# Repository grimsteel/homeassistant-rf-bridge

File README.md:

# Home Assistant RF + IR Bridge

A wireless module for adding RF and IR capabilities to Home Assistant. Built on an ESP32-S2. Uses the MQTT protocol.

## Firmware

A template ESPHome firmware is included in the `esphome` dir.

## Case

Case coming soon!

## PCB

* Front: includes pin sockets for two CC1101 modules. (allows for RX/TX on multiple freqs if needed)
* Back: space for two 6mm buttons, two IR leds, and one IR receiver.

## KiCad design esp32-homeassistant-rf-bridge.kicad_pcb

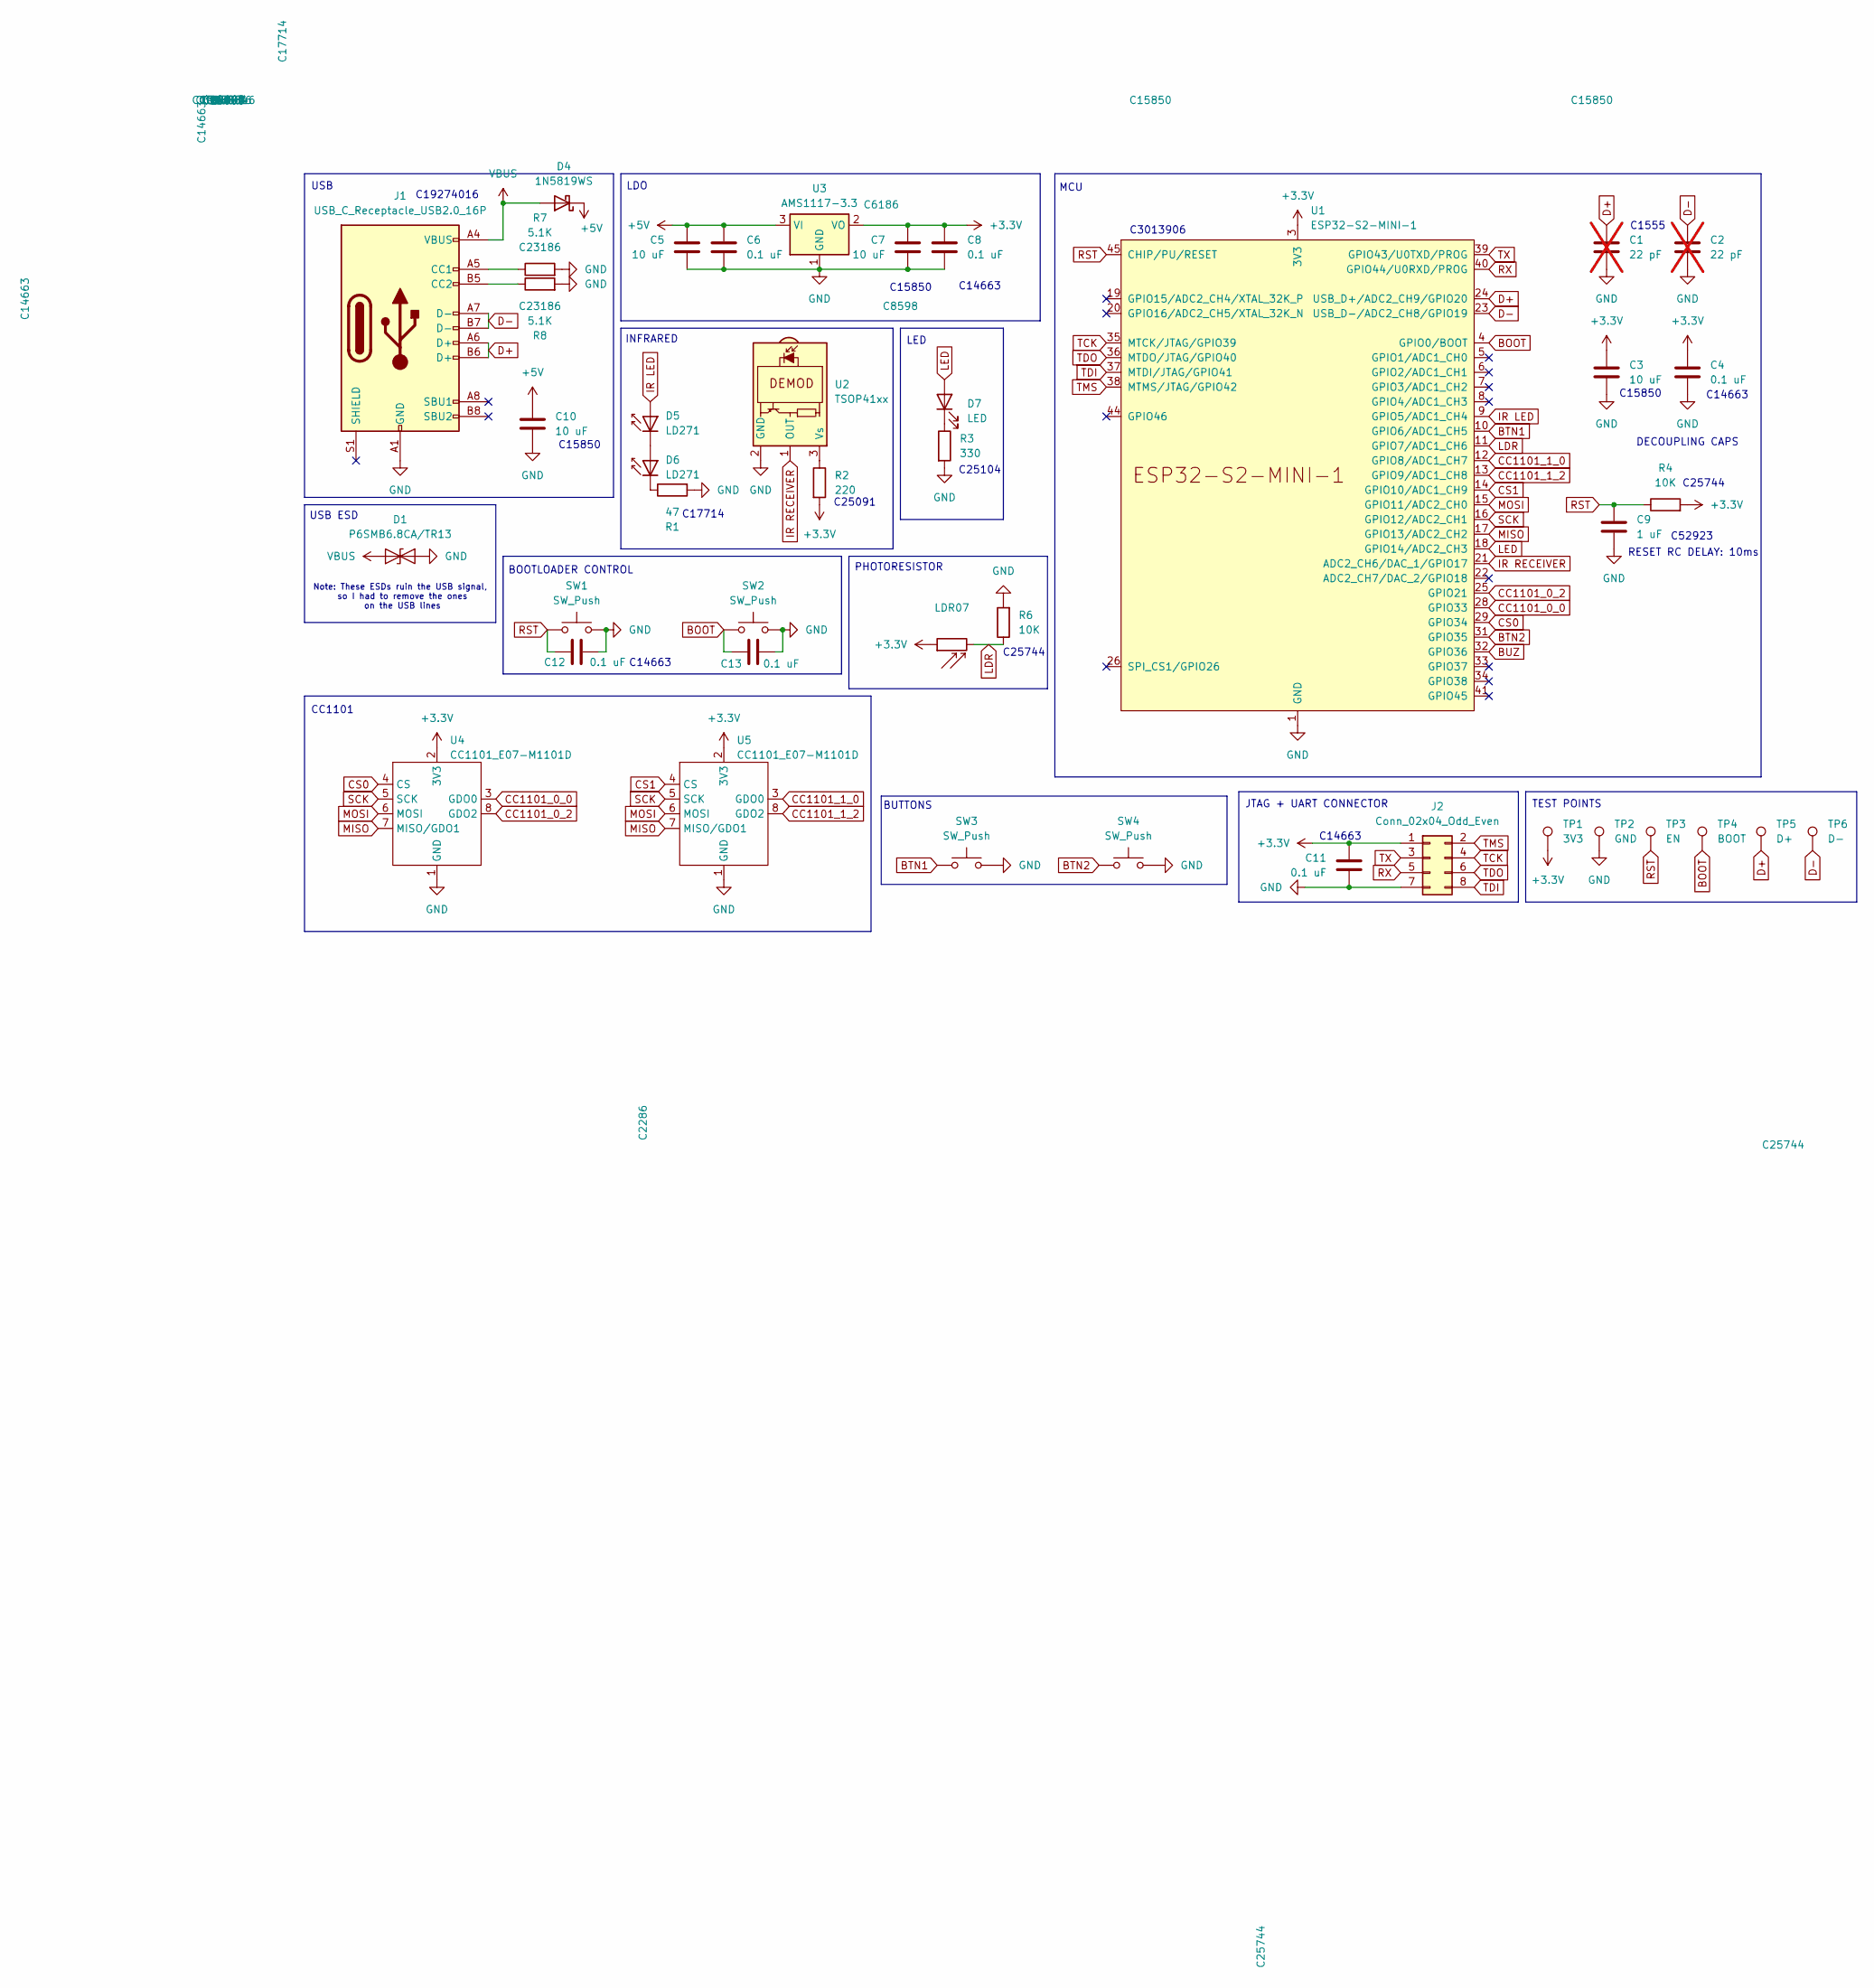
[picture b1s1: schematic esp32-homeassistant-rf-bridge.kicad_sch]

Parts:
C1, C2: 22 pF; C_0402_1005Metric; LCSC C1555; not fitted
C3, C5, C7, C10: 10 uF; C_0805_2012Metric; LCSC C15850
C4, C6, C8, C11, C12, C13: 0.1 uF; C_0603_1608Metric; LCSC C14663
C9: 1 uF; C_0402_1005Metric; LCSC C52923
D1: P6SMB6.8CA/TR13; D_SMB; LCSC C78395
D4: 1N5819WS; D_SOD-123; LCSC C8598
D5, D6: LD271; LED_D5.0mm_IRGrey
D7: LED; LED_0603_1608Metric; LCSC C2286
J1: USB_C_Receptacle_USB2.0_16P; USB_C_Receptacle_HCTL_HC-TYPE-C-16P-01A; LCSC C19274016
J2: Conn_02x04_Odd_Even; PinHeader_2x04_P2.54mm_Vertical
LDR07: R_LDR_5.0x4.1mm_P3mm_Vertical
R1: 47; R_0805_2012Metric; LCSC C17714
R2: 220; R_0402_1005Metric; LCSC C25091
R3: 330; R_0402_1005Metric; LCSC C25104
R4, R6: 10K; R_0402_1005Metric; LCSC C25744
R7, R8: 5.1K; R_0603_1608Metric; LCSC C23186
SW1, SW2: SW_Push; SW_Push_1P1T_XKB_TS-1187A; LCSC C318884
SW3, SW4: SW_Push; SW_PUSH_6mm
TP1: 3V3; TestPoint_Pad_D3.0mm
TP2: GND; TestPoint_Pad_D3.0mm
TP3: EN; TestPoint_Pad_D3.0mm
TP4: BOOT; TestPoint_Pad_D3.0mm
TP5: D+; TestPoint_Pad_D3.0mm
TP6: D-; TestPoint_Pad_D3.0mm
U1: ESP32-S2-MINI-1; LCSC C3013906
U2: TSOP41xx; Vishay_MOLD-3Pin
U3: AMS1117-3.3; SOT-223-3_TabPin2; LCSC C6186
U4, U5: CC1101_E07-M1101D; CC1101_E07-MM1101D-TH

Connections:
+3.3V: C3.1, C4.1, C7.1, C8.1, C11.1, J2.1, LDR07.1, R2.2, R4.2, TP1.1, U1.3 (3V3), U3.2 (VO), U4.2 (3V3), U5.2 (3V3)
+5V: C5.1, C6.1, C10.1, D4.1 (K), U3.3 (VI)
BOOT: C13.1, SW2.1, TP4.1, U1.4 (GPIO0/BOOT)
BTN1: SW3.1, U1.10 (GPIO6/ADC1_CH5)
BTN2: SW4.1, U1.31 (GPIO35)
BUZ: U1.32 (GPIO36)
CC1101_0_0: U1.28 (GPIO33), U4.3 (GDO0)
CC1101_0_2: U1.25 (GPIO21), U4.8 (GDO2)
CC1101_1_0: U1.12 (GPIO8/ADC1_CH7), U5.3 (GDO0)
CC1101_1_2: U1.13 (GPIO9/ADC1_CH8), U5.8 (GDO2)
CS0: U1.29 (GPIO34), U4.4 (CS)
CS1: U1.14 (GPIO10/ADC1_CH9), U5.4 (CS)
D+: C1.1, J1.A6 (D+), J1.B6 (D+), TP5.1, U1.24 (USB_D+/ADC2_CH9/GPIO20)
D-: C2.1, J1.A7 (D-), J1.B7 (D-), TP6.1, U1.23 (USB_D-/ADC2_CH8/GPIO19)
GND: C1.2, C2.2, C3.2, C4.2, C5.2, C6.2, C7.2, C8.2, C9.2, C10.2, C11.2, C12.2, C13.2, D1.2 (A2), J1.A1 (GND), J1.A12 (GND), J1.B1 (GND), J1.B12 (GND), J2.7, R1.2, R3.2, R6.2, R7.2, R8.2, SW1.2, SW2.2, SW3.2, SW4.2, TP2.1, U1.1 (GND), U1.2 (GND), U1.30 (GND), U1.42 (GND), U1.43 (GND), U1.46 (GND), U1.47 (GND), U1.48 (GND), U1.49 (GND), U1.50 (GND), U1.51 (GND), U1.52 (GND), U1.53 (GND), U1.54 (GND), U1.55 (GND), U1.56 (GND), U1.57 (GND), U1.58 (GND), U1.59 (GND), U1.60 (GND), U1.61 (GND), U1.62 (GND), U1.63 (GND), U1.64 (GND), U1.65 (GND), U2.2 (GND), U3.1 (GND), U4.1 (GND), U5.1 (GND)
IR LED: D5.2 (A), U1.9 (GPIO5/ADC1_CH4)
IR RECEIVER: U1.21 (ADC2_CH6/DAC_1/GPIO17), U2.1 (OUT)
LDR: LDR07.2, R6.1, U1.11 (GPIO7/ADC1_CH6)
LED: D7.2 (A), U1.18 (GPIO14/ADC2_CH3)
MISO: U1.17 (GPIO13/ADC2_CH2), U4.7 (MISO/GDO1), U5.7 (MISO/GDO1)
MOSI: U1.15 (GPIO11/ADC2_CH0), U4.6 (MOSI), U5.6 (MOSI)
unnamed: D5.1 (K), D6.2 (A)
unnamed: D6.1 (K), R1.1
unnamed: D7.1 (K), R3.1
unnamed: J1.A5 (CC1), R7.1
unnamed: J1.B5 (CC2), R8.1
unnamed: R2.1, U2.3 (Vs)
RST: C9.1, C12.1, R4.1, SW1.1, TP3.1, U1.45 (CHIP/PU/RESET)
RX: J2.5, U1.40 (GPIO44/U0RXD/PROG)
SCK: U1.16 (GPIO12/ADC2_CH1), U4.5 (SCK), U5.5 (SCK)
TCK: J2.4, U1.35 (MTCK/JTAG/GPIO39)
TDI: J2.8, U1.37 (MTDI/JTAG/GPIO41)
TDO: J2.6, U1.36 (MTDO/JTAG/GPIO40)
TMS: J2.2, U1.38 (MTMS/JTAG/GPIO42)
TX: J2.3, U1.39 (GPIO43/U0TXD/PROG)
VBUS: D1.1 (A1), D4.2 (A), J1.A4 (VBUS), J1.A9 (VBUS), J1.B4 (VBUS), J1.B9 (VBUS)

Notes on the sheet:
C14663
C25104
LED
LDO
C1555
C52923
BUTTONS
INFRARED
CC1101
MCU
PHOTORESISTOR
TEST POINTS
C17714
JTAG + UART CONNECTOR
C25091
C15850
Note: These ESDs ruin the USB signal, so I had to remove the ones on the USB lines
USB
C25744
DECOUPLING CAPS
RESET RC DELAY: 10ms
C19274016
C3013906
BOOTLOADER CONTROL
USB ESD

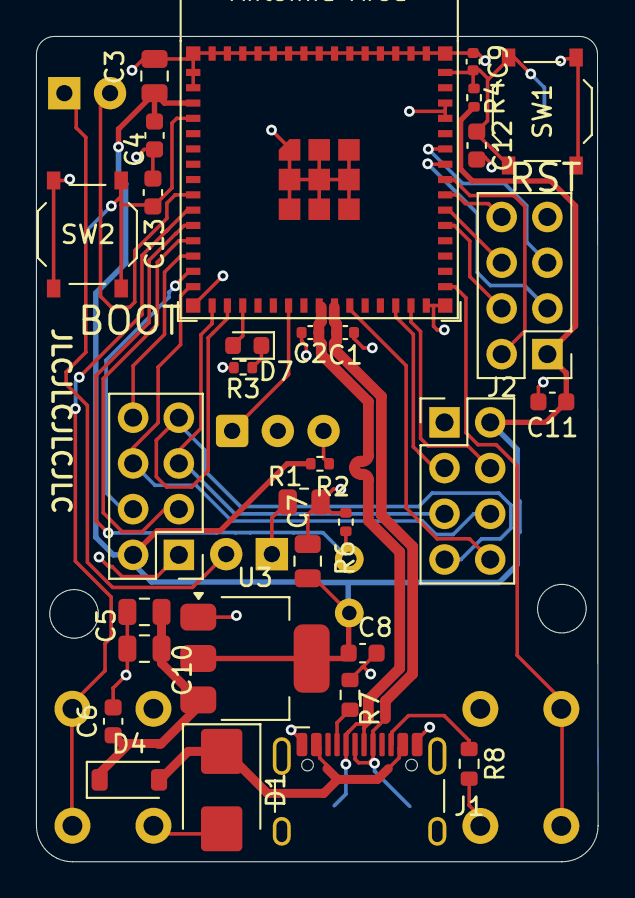
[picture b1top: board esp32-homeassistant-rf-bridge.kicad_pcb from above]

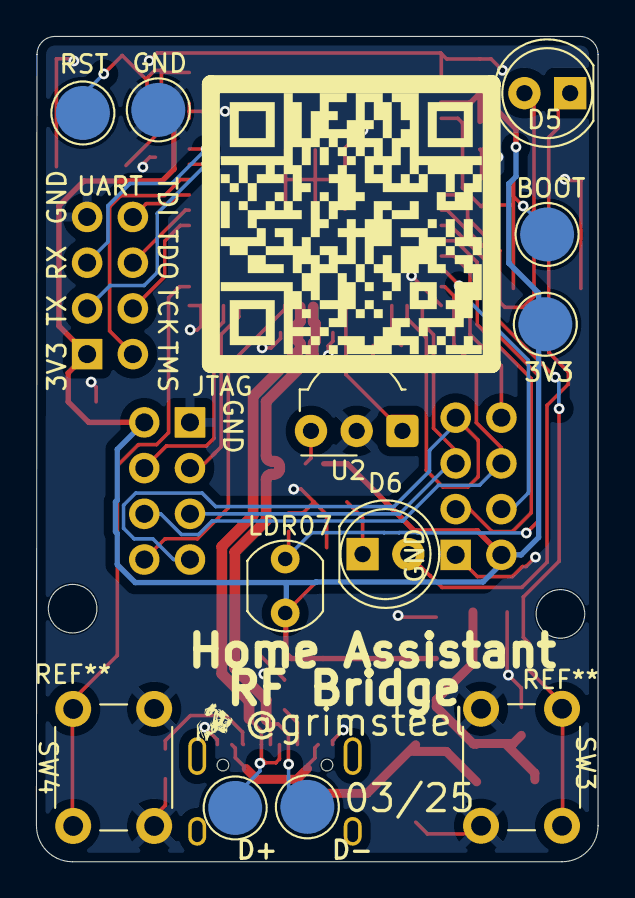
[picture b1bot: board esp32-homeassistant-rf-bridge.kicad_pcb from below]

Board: 2 copper layers, 31.2 x 45.8 mm, 44 parts (13 on the bottom side), 35 nets.

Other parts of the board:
QR*****: qrcode

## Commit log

2024-12-30 add readme + license
2024-12-30 update some silkscreen stuff
2024-12-30 add more 3d models
2024-12-30 update production files
2024-12-30 add JLCPCB ID designator
2024-12-31 silkscreen updates, add LDR and mounting holes
2025-01-17 make board smaller, remove problematic components
2025-03-21 add firmware
2025-03-21 use ams1117
2025-07-05 reduce mounting point size
